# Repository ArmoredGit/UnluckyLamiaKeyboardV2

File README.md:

# UnluckyLamiaKeyboardV2
Wireless split stenography keyboard for laptop use

the following is an example layout as would be pictured on keycaps

Current progress
 - size and specifications decided
 - ergogen used to generate basic pcb
 - pcb routing
 
TODO
 - writing ZMK firmware
 - case and carrying case design
 - renders
 - pruduction

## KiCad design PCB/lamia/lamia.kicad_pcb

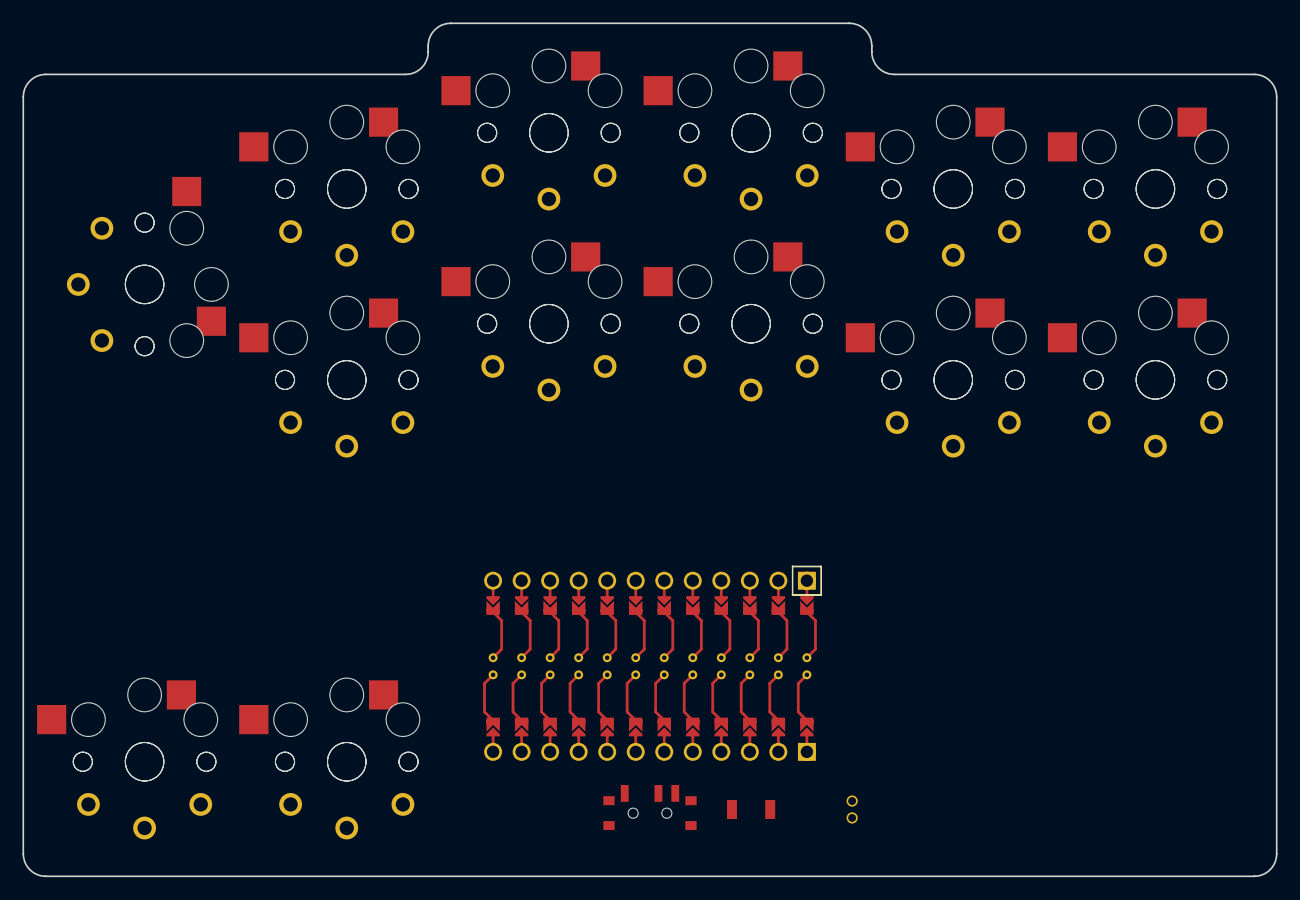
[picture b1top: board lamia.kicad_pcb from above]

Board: 2 copper layers, 111.6 x 76.0 mm, 27 parts (0 on the bottom side), 14 nets, no tracks yet.

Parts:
MCU1: ProMicro
S1, S2, S3, S4, S5, S6, S7, S8, S9, S10, S11, S12, S13, S14, S15, S16, S17, S18, S19, S20, S21, S22, S23, S24, S25, S26: PG1350

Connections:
GND: MCU1.2, MCU1.21, MCU1.22, S1.2, S2.2, S3.2, S4.2, S5.2, S6.2, S7.2, S8.2, S9.2, S10.2, S11.2, S12.2, S13.2, S14.2, S15.2, S16.2, S17.2, S18.2, S19.2, S20.2, S21.2, S22.2, S23.2, S24.2, S25.2, S26.2
P4: MCU1.18, S17.1, S18.1
P5: MCU1.17, S13.1, S14.1
P6: MCU1.16, S9.1, S10.1
P7: MCU1.15, S5.1, S6.1
P8: MCU1.14, S3.1, S4.1
P9: MCU1.13, S1.1, S2.1
P10: MCU1.12, S23.1, S24.1
P15: MCU1.9, S7.1, S8.1
P16: MCU1.11, S25.1, S26.1
P18: MCU1.8, S11.1, S12.1
P19: MCU1.7, S15.1, S16.1
P20: MCU1.6, S21.1, S22.1
P21: MCU1.5, S19.1, S20.1

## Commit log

2022-08-09 init comit
2022-08-10 all pcb nets set
2022-08-10 filled in the blanks
2022-08-10 read me touches
2022-08-11 PCB routing
